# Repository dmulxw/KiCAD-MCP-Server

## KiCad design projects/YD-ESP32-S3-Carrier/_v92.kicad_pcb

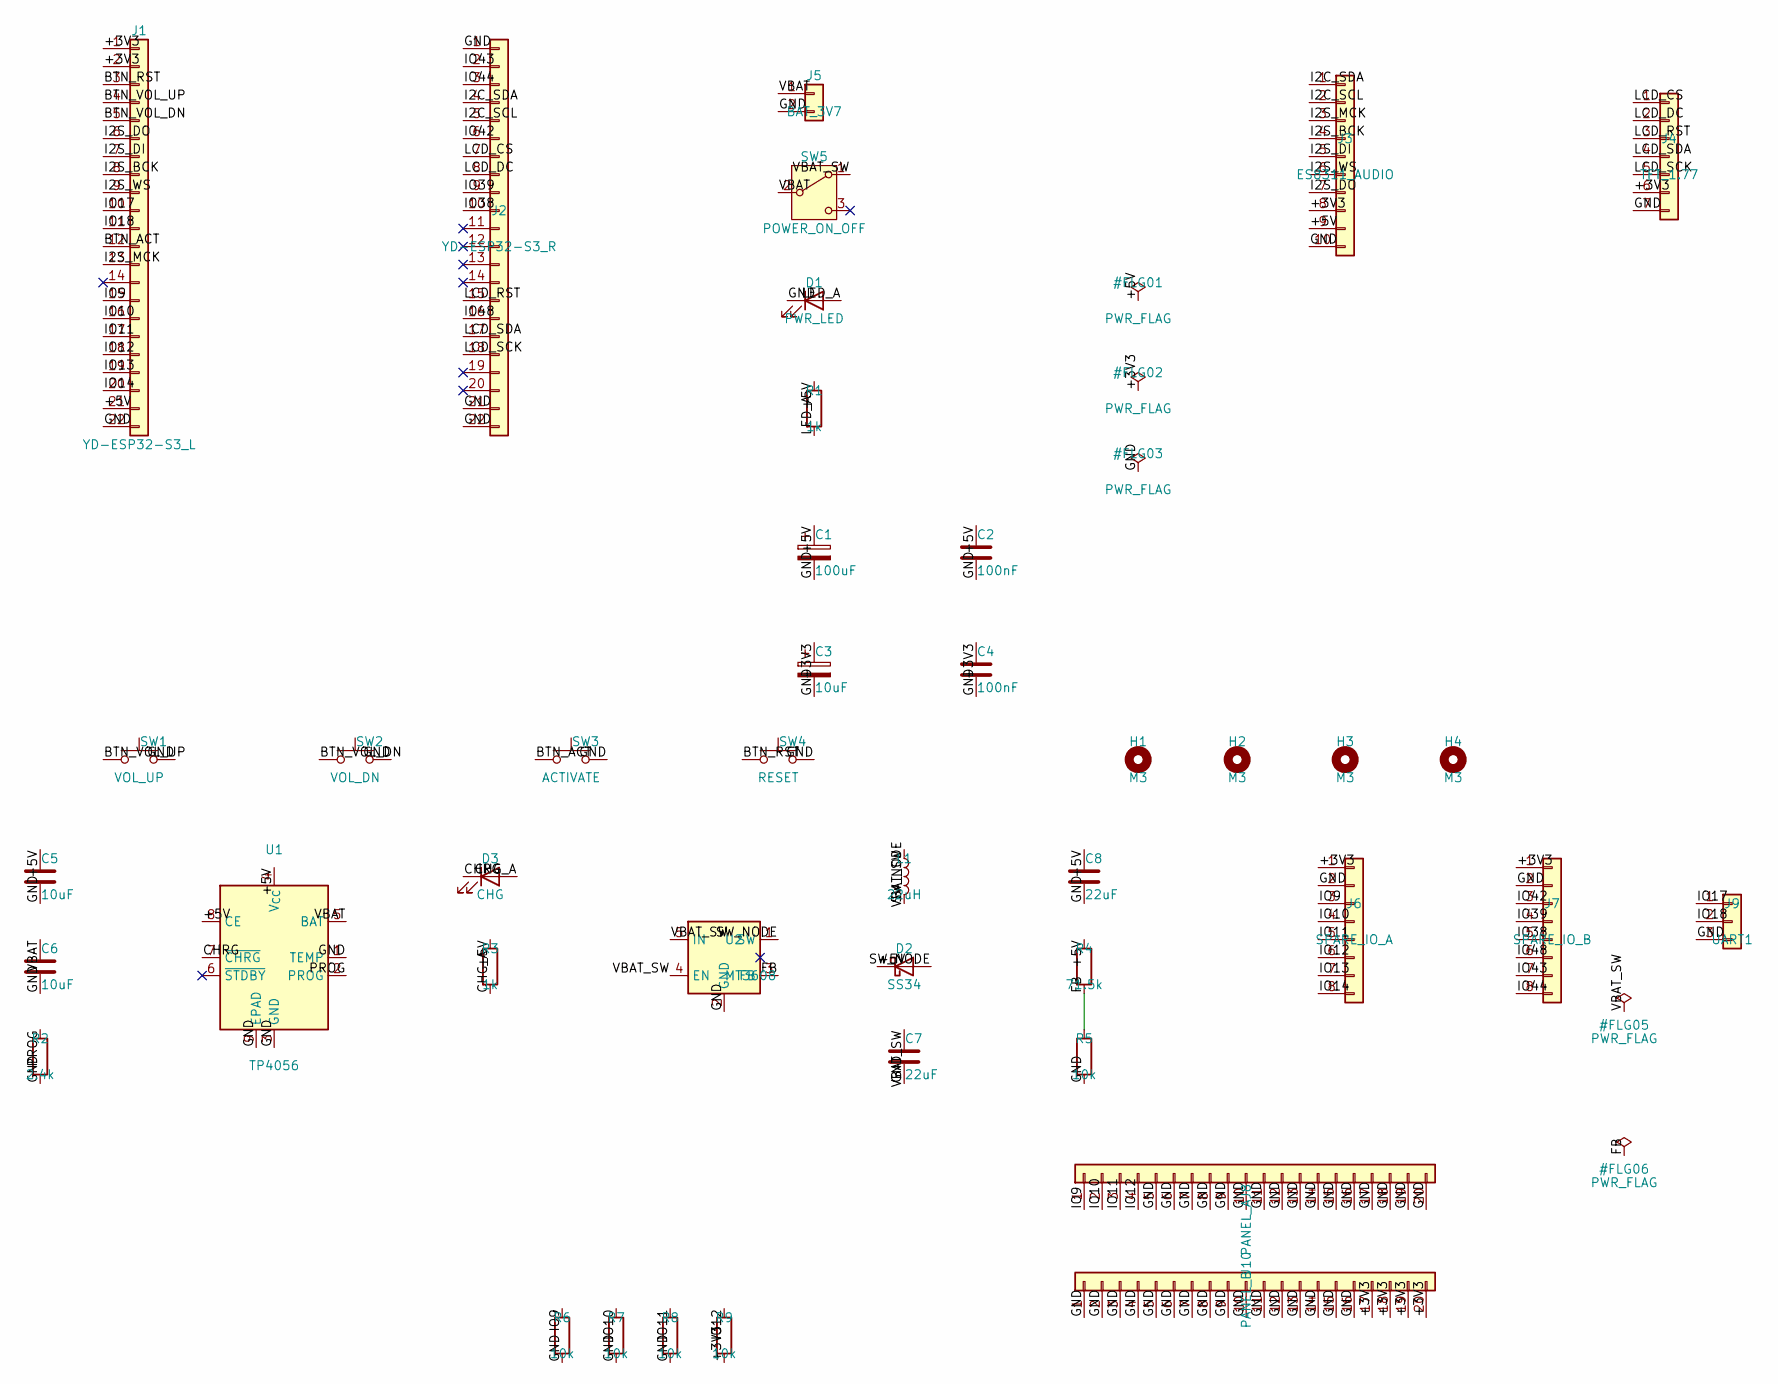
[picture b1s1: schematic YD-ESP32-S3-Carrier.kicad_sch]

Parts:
C1: 100uF; CP_Radial_D5.0mm_P2.50mm
C2, C4: 100nF; C_Disc_D5.0mm_W2.5mm_P5.00mm
C3: 10uF; CP_Radial_D5.0mm_P2.50mm
C5, C6: 10uF; C_1206_3216Metric
C7, C8: 22uF; C_1206_3216Metric
D1: PWR_LED; LED_D5.0mm
D2: SS34; D_SMA
D3: CHG; LED_0805_2012Metric
H1, H2, H3, H4: M3; MountingHole_3.2mm_M3
J1: YD-ESP32-S3_L; PinSocket_1x22_P2.54mm_Vertical
J2: YD-ESP32-S3_R; PinSocket_1x22_P2.54mm_Vertical
J3: ES8311_AUDIO; PinSocket_1x10_P2.54mm_Vertical
J4: TFT_1.77; PinHeader_1x07_P2.54mm_Vertical
J5: BAT_3V7; PinHeader_1x02_P2.54mm_Vertical
J6: SPARE_IO_A; PinHeader_1x08_P2.54mm_Vertical
J7: SPARE_IO_B; PinHeader_1x08_P2.54mm_Vertical
J8: PANEL_A; PinHeader_1x20_P2.54mm_Vertical
J9: UART1; PinHeader_1x03_P2.54mm_Vertical
J10: PANEL_B; PinHeader_1x20_P2.54mm_Vertical
L1: 22uH; L_Taiyo-Yuden_NR-60xx
R1: 1k; R_Axial_DIN0207_L6.3mm_D2.5mm_P7.62mm_Horizontal
R2: 2.4k; R_0805_2012Metric
R3: 1k; R_0805_2012Metric
R4: 71.5k; R_0805_2012Metric
R5: 10k; R_0805_2012Metric
R6, R7, R8, R9: 10k; R_0603_1608Metric
SW1: VOL_UP; SW_PUSH_6mm
SW2: VOL_DN; SW_PUSH_6mm
SW3: ACTIVATE; SW_PUSH_6mm
SW4: RESET; SW_PUSH_6mm
SW5: POWER_ON_OFF; SW_Slide_SPDT_Straight_CK_OS102011MS2Q
U1: TP4056; SOIC-8-1EP_3.9x4.9mm_P1.27mm_EP2.41x3.3mm_ThermalVias
U2: MT3608; SOT-23-6

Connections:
+3V3: C3.1, C4.1, J1.1, J1.2, J3.8, J4.6, J6.1, J7.1, J10.17, J10.18, J10.19, J10.20, R9.2
+5V: C1.1, C2.1, C5.1, C8.1, D2.1 (K), J1.21, J3.9, R1.1, R3.1, R4.1, U1.4 (V_{CC}), U1.8 (CE)
BTN_ACT: J1.12, SW3.1
BTN_RST: J1.3, SW4.1
BTN_VOL_DN: J1.5, SW2.1
BTN_VOL_UP: J1.4, SW1.1
CHG_A: D3.2 (A), R3.2
CHRG: D3.1 (K), U1.7 (~CHRG)
FB: R4.2, R5.1, U2.3 (FB)
GND: C1.2, C2.2, C3.2, C4.2, C5.2, C6.2, C7.2, C8.2, D1.1 (K), J1.22, J2.1, J2.21, J2.22, J3.10, J4.7, J5.2, J6.2, J7.2, J8.5, J8.6, J8.7, J8.8, J8.9, J8.10, J8.11, J8.12, J8.13, J8.14, J8.15, J8.16, J8.17, J8.18, J8.19, J8.20, J9.3, J10.1, J10.2, J10.3, J10.4, J10.5, J10.6, J10.7, J10.8, J10.9, J10.10, J10.11, J10.12, J10.13, J10.14, J10.15, J10.16, R2.2, R5.2, R6.2, R7.2, R8.2, SW1.2, SW2.2, SW3.2, SW4.2, U1.1 (TEMP), U1.3 (GND), U1.9 (EPAD), U2.2 (GND)
I2C_SCL: J2.5, J3.2
I2C_SDA: J2.4, J3.1
I2S_BCK: J1.8, J3.4
I2S_DI: J1.7, J3.5
I2S_DO: J1.6, J3.7
I2S_MCK: J1.13, J3.3
I2S_WS: J1.9, J3.6
IO9: J1.15, J6.3, J8.1, R6.1
IO10: J1.16, J6.4, J8.2, R7.1
IO11: J1.17, J6.5, J8.3, R8.1
IO12: J1.18, J6.6, J8.4, R9.1
IO13: J1.19, J6.7
IO14: J1.20, J6.8
IO17: J1.10, J9.1
IO18: J1.11, J9.2
IO38: J2.10, J7.5
IO39: J2.9, J7.4
IO42: J2.6, J7.3
IO43: J2.2, J7.7
IO44: J2.3, J7.8
IO48: J2.16, J7.6
LCD_CS: J2.7, J4.1
LCD_DC: J2.8, J4.2
LCD_RST: J2.15, J4.3
LCD_SCK: J2.18, J4.5
LCD_SDA: J2.17, J4.4
LED_A: D1.2 (A), R1.2
PROG: R2.1, U1.2 (PROG)
SW_NODE: D2.2 (A), L1.2, U2.1 (SW)
VBAT: C6.1, J5.1, SW5.2 (B), U1.5 (BAT)
VBAT_SW: C7.1, L1.1, SW5.1 (A), U2.4 (EN), U2.5 (IN)

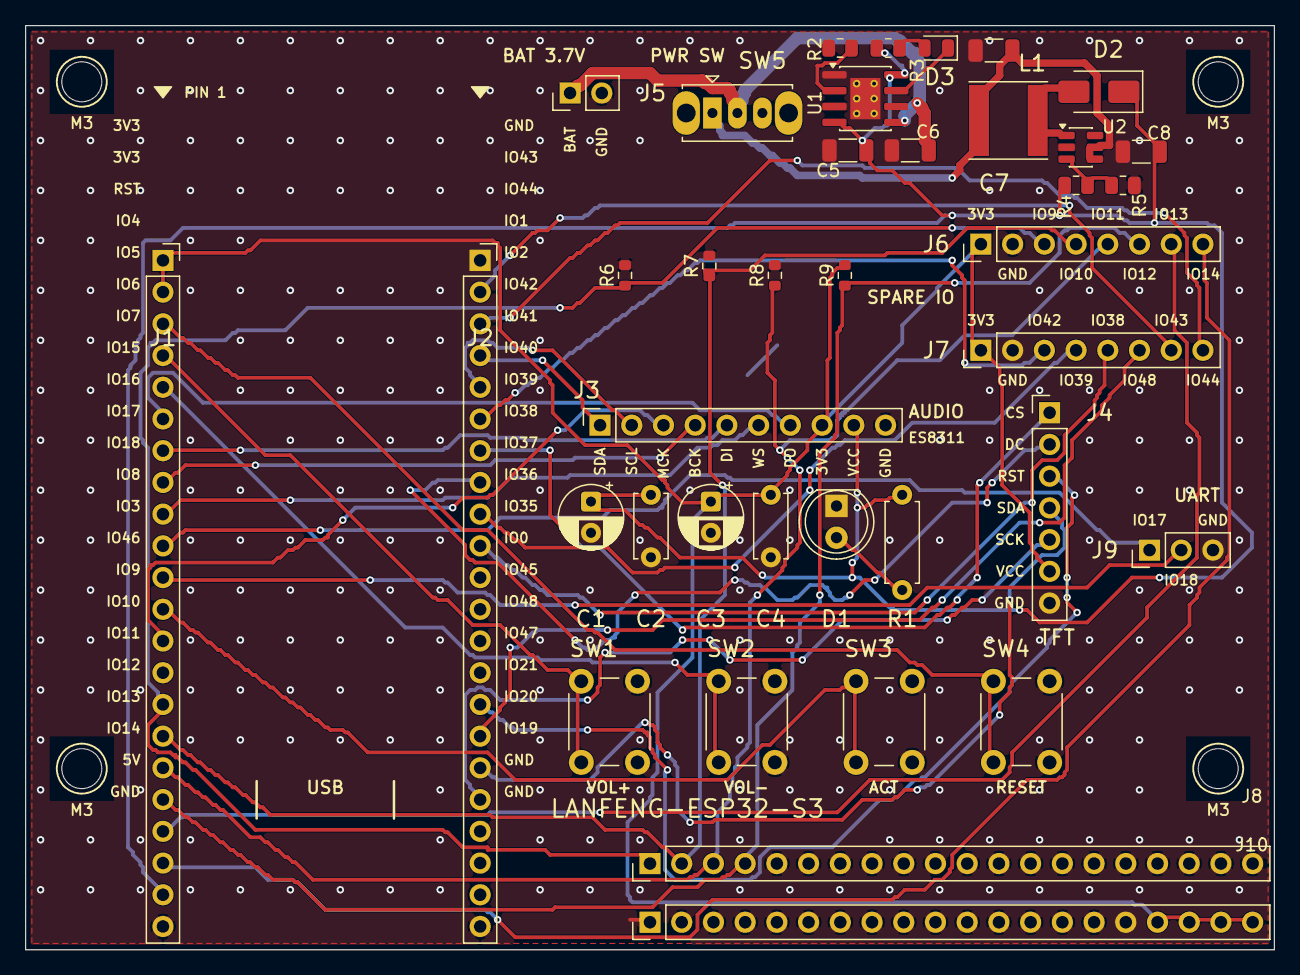
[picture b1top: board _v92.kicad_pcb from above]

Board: 2 copper layers, 100.0 x 74.0 mm, 42 parts (0 on the bottom side), 41 nets.

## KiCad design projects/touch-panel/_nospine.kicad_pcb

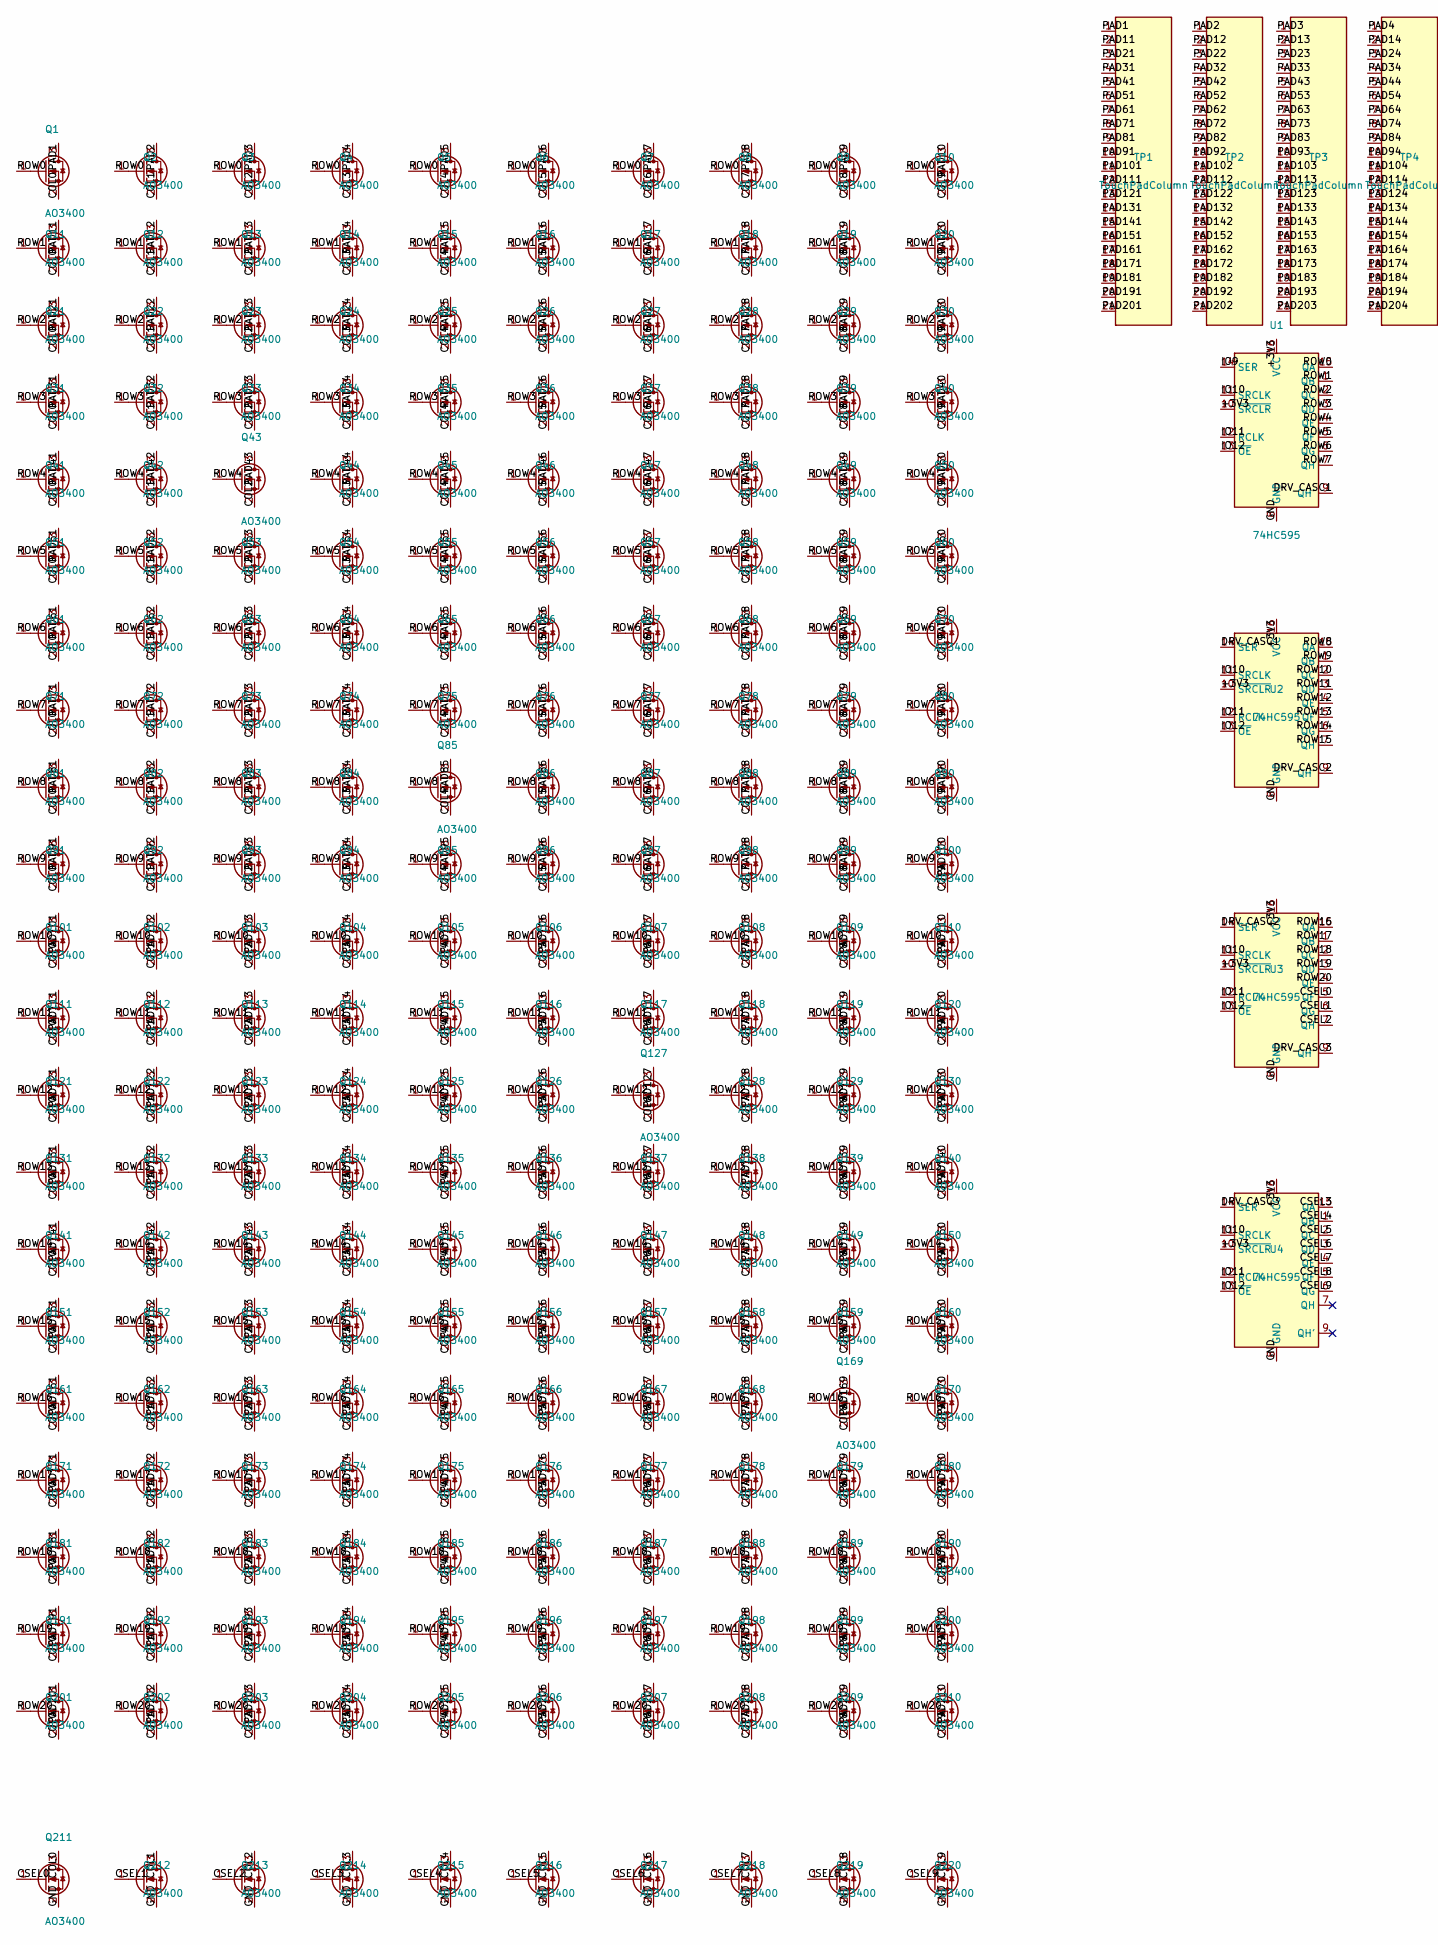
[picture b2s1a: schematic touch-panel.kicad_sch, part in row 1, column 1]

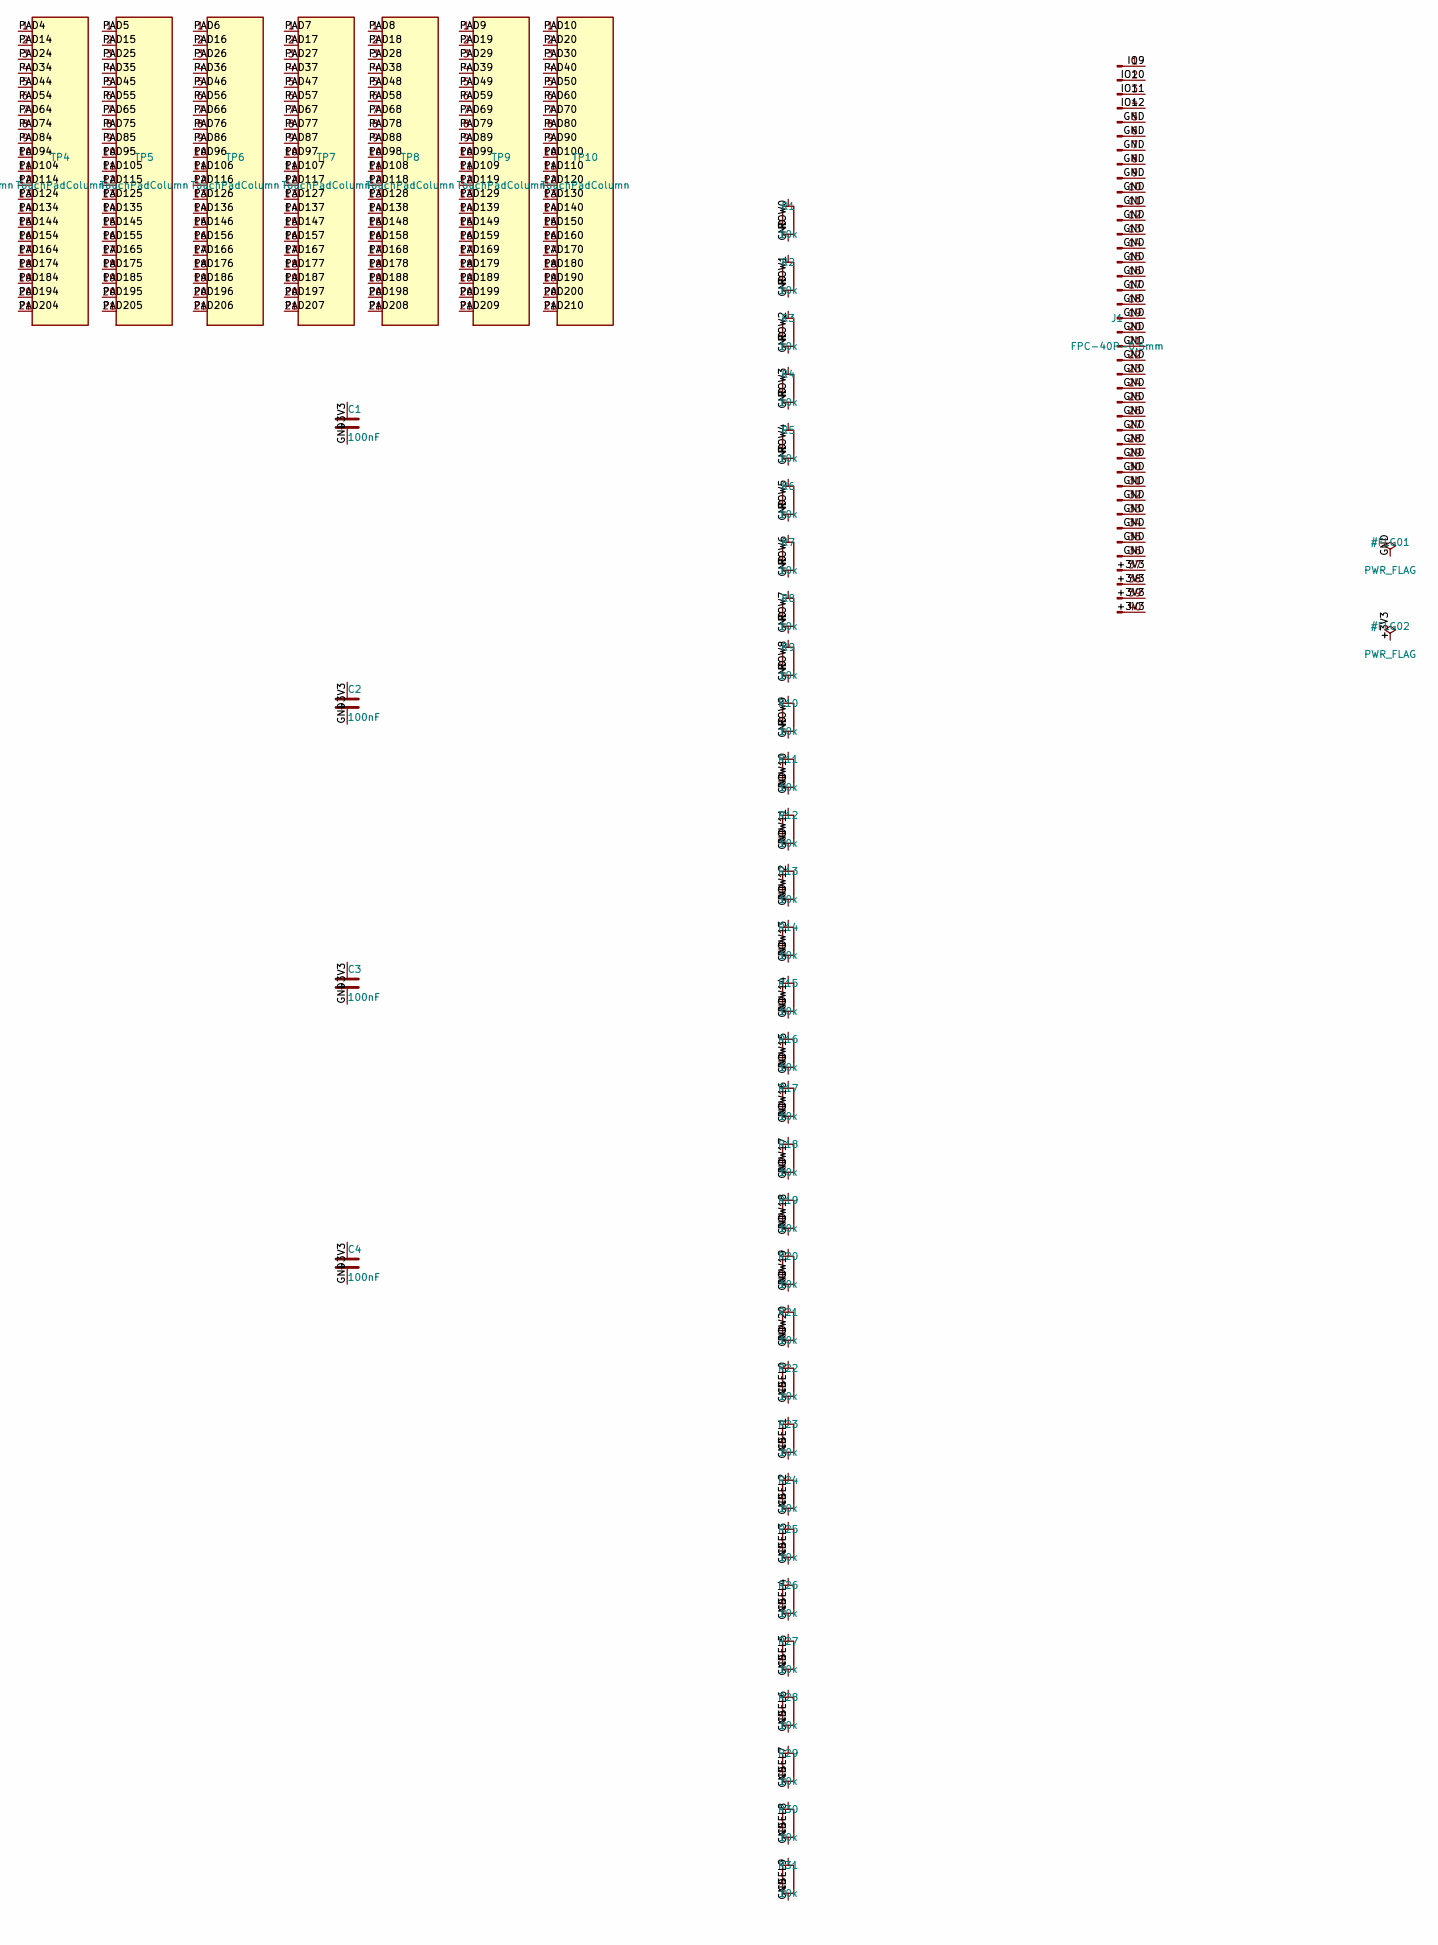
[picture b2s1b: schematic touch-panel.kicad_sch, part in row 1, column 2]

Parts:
C1, C2, C3, C4: 100nF; C_0402_1005Metric
J1: FPC-40P-0.5mm; Hirose_FH12-40S-0.5SH_1x40-1MP_P0.50mm_Horizontal
Q1, Q2, Q3, Q4, Q5, Q6, Q7, Q8, Q9, Q10, Q11, Q12, Q13, Q14, Q15, Q16, Q17, Q18, Q19, Q20, Q21, Q22, Q23, Q24, Q25, Q26, Q27, Q28, Q29, Q30, Q31, Q32, Q33, Q34, Q35, Q36, Q37, Q38, Q39, Q40, Q41, Q42, Q43, Q44, Q45, Q46, Q47, Q48, Q49, Q50, Q51, Q52, Q53, Q54, Q55, Q56, Q57, Q58, Q59, Q60, Q61, Q62, Q63, Q64, Q65, Q66, Q67, Q68, Q69, Q70, Q71, Q72, Q73, Q74, Q75, Q76, Q77, Q78, Q79, Q80, Q81, Q82, Q83, Q84, Q85, Q86, Q87, Q88, Q89, Q90, Q91, Q92, Q93, Q94, Q95, Q96, Q97, Q98, Q99, Q100, Q101, Q102, Q103, Q104, Q105, Q106, Q107, Q108, Q109, Q110, Q111, Q112, Q113, Q114, Q115, Q116, Q117, Q118, Q119, Q120, Q121, Q122, Q123, Q124, Q125, Q126, Q127, Q128, Q129, Q130, Q131, Q132, Q133, Q134, Q135, Q136, Q137, Q138, Q139, Q140, Q141, Q142, Q143, Q144, Q145, Q146, Q147, Q148, Q149, Q150, Q151, Q152, Q153, Q154, Q155, Q156, Q157, Q158, Q159, Q160, Q161, Q162, Q163, Q164, Q165, Q166, Q167, Q168, Q169, Q170, Q171, Q172, Q173, Q174, Q175, Q176, Q177, Q178, Q179, Q180, Q181, Q182, Q183, Q184, Q185, Q186, Q187, Q188, Q189, Q190, Q191, Q192, Q193, Q194, Q195, Q196, Q197, Q198, Q199, Q200, Q201, Q202, Q203, Q204, Q205, Q206, Q207, Q208, Q209, Q210, Q211, Q212, Q213, Q214, Q215, Q216, Q217, Q218, Q219, Q220: AO3400; SOT-23
R1, R2, R3, R4, R5, R6, R7, R8, R9, R10, R11, R12, R13, R14, R15, R16, R17, R18, R19, R20, R21, R22, R23, R24, R25, R26, R27, R28, R29, R30, R31: 10k; R_0402_1005Metric
TP1, TP2, TP3, TP4, TP5, TP6, TP7, TP8, TP9, TP10: TouchPadColumn
U1, U2, U3, U4: 74HC595; SOIC-16_3.9x9.9mm_P1.27mm

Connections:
+3V3: C1.1, C2.1, C3.1, C4.1, J1.37, J1.38, J1.39, J1.40, U1.10 (~SRCLR), U1.16 (VCC), U2.10 (~SRCLR), U2.16 (VCC), U3.10 (~SRCLR), U3.16 (VCC), U4.10 (~SRCLR), U4.16 (VCC)
COL0: Q1.2 (S), Q11.2 (S), Q21.2 (S), Q31.2 (S), Q41.2 (S), Q51.2 (S), Q61.2 (S), Q71.2 (S), Q81.2 (S), Q91.2 (S), Q101.2 (S), Q111.2 (S), Q121.2 (S), Q131.2 (S), Q141.2 (S), Q151.2 (S), Q161.2 (S), Q171.2 (S), Q181.2 (S), Q191.2 (S), Q201.2 (S), Q211.3 (D)
COL1: Q2.2 (S), Q12.2 (S), Q22.2 (S), Q32.2 (S), Q42.2 (S), Q52.2 (S), Q62.2 (S), Q72.2 (S), Q82.2 (S), Q92.2 (S), Q102.2 (S), Q112.2 (S), Q122.2 (S), Q132.2 (S), Q142.2 (S), Q152.2 (S), Q162.2 (S), Q172.2 (S), Q182.2 (S), Q192.2 (S), Q202.2 (S), Q212.3 (D)
COL2: Q3.2 (S), Q13.2 (S), Q23.2 (S), Q33.2 (S), Q43.2 (S), Q53.2 (S), Q63.2 (S), Q73.2 (S), Q83.2 (S), Q93.2 (S), Q103.2 (S), Q113.2 (S), Q123.2 (S), Q133.2 (S), Q143.2 (S), Q153.2 (S), Q163.2 (S), Q173.2 (S), Q183.2 (S), Q193.2 (S), Q203.2 (S), Q213.3 (D)
COL3: Q4.2 (S), Q14.2 (S), Q24.2 (S), Q34.2 (S), Q44.2 (S), Q54.2 (S), Q64.2 (S), Q74.2 (S), Q84.2 (S), Q94.2 (S), Q104.2 (S), Q114.2 (S), Q124.2 (S), Q134.2 (S), Q144.2 (S), Q154.2 (S), Q164.2 (S), Q174.2 (S), Q184.2 (S), Q194.2 (S), Q204.2 (S), Q214.3 (D)
COL4: Q5.2 (S), Q15.2 (S), Q25.2 (S), Q35.2 (S), Q45.2 (S), Q55.2 (S), Q65.2 (S), Q75.2 (S), Q85.2 (S), Q95.2 (S), Q105.2 (S), Q115.2 (S), Q125.2 (S), Q135.2 (S), Q145.2 (S), Q155.2 (S), Q165.2 (S), Q175.2 (S), Q185.2 (S), Q195.2 (S), Q205.2 (S), Q215.3 (D)
COL5: Q6.2 (S), Q16.2 (S), Q26.2 (S), Q36.2 (S), Q46.2 (S), Q56.2 (S), Q66.2 (S), Q76.2 (S), Q86.2 (S), Q96.2 (S), Q106.2 (S), Q116.2 (S), Q126.2 (S), Q136.2 (S), Q146.2 (S), Q156.2 (S), Q166.2 (S), Q176.2 (S), Q186.2 (S), Q196.2 (S), Q206.2 (S), Q216.3 (D)
COL6: Q7.2 (S), Q17.2 (S), Q27.2 (S), Q37.2 (S), Q47.2 (S), Q57.2 (S), Q67.2 (S), Q77.2 (S), Q87.2 (S), Q97.2 (S), Q107.2 (S), Q117.2 (S), Q127.2 (S), Q137.2 (S), Q147.2 (S), Q157.2 (S), Q167.2 (S), Q177.2 (S), Q187.2 (S), Q197.2 (S), Q207.2 (S), Q217.3 (D)
COL7: Q8.2 (S), Q18.2 (S), Q28.2 (S), Q38.2 (S), Q48.2 (S), Q58.2 (S), Q68.2 (S), Q78.2 (S), Q88.2 (S), Q98.2 (S), Q108.2 (S), Q118.2 (S), Q128.2 (S), Q138.2 (S), Q148.2 (S), Q158.2 (S), Q168.2 (S), Q178.2 (S), Q188.2 (S), Q198.2 (S), Q208.2 (S), Q218.3 (D)
COL8: Q9.2 (S), Q19.2 (S), Q29.2 (S), Q39.2 (S), Q49.2 (S), Q59.2 (S), Q69.2 (S), Q79.2 (S), Q89.2 (S), Q99.2 (S), Q109.2 (S), Q119.2 (S), Q129.2 (S), Q139.2 (S), Q149.2 (S), Q159.2 (S), Q169.2 (S), Q179.2 (S), Q189.2 (S), Q199.2 (S), Q209.2 (S), Q219.3 (D)
COL9: Q10.2 (S), Q20.2 (S), Q30.2 (S), Q40.2 (S), Q50.2 (S), Q60.2 (S), Q70.2 (S), Q80.2 (S), Q90.2 (S), Q100.2 (S), Q110.2 (S), Q120.2 (S), Q130.2 (S), Q140.2 (S), Q150.2 (S), Q160.2 (S), Q170.2 (S), Q180.2 (S), Q190.2 (S), Q200.2 (S), Q210.2 (S), Q220.3 (D)
CSEL0: Q211.1 (G), R22.1, U3.5 (QF)
CSEL1: Q212.1 (G), R23.1, U3.6 (QG)
CSEL2: Q213.1 (G), R24.1, U3.7 (QH)
CSEL3: Q214.1 (G), R25.1, U4.15 (QA); also elsewhere on the board
CSEL4: Q215.1 (G), R26.1, U4.1 (QB); also elsewhere on the board
CSEL5: Q216.1 (G), R27.1, U4.2 (QC); also elsewhere on the board
CSEL6: Q217.1 (G), R28.1, U4.3 (QD); also elsewhere on the board
CSEL7: Q218.1 (G), R29.1, U4.4 (QE)
CSEL8: Q219.1 (G), R30.1, U4.5 (QF)
CSEL9: Q220.1 (G), R31.1, U4.6 (QG)
DRV_CASC1: U1.9 (QH'), U2.14 (SER)
DRV_CASC2: U2.9 (QH'), U3.14 (SER)
DRV_CASC3: U3.9 (QH'), U4.14 (SER)
GND: C1.2, C2.2, C3.2, C4.2, J1.5, J1.6, J1.7, J1.8, J1.9, J1.10, J1.11, J1.12, J1.13, J1.14, J1.15, J1.16, J1.17, J1.18, J1.19, J1.20, J1.21, J1.22, J1.23, J1.24, J1.25, J1.26, J1.27, J1.28, J1.29, J1.30, J1.31, J1.32, J1.33, J1.34, J1.35, J1.36, Q211.2 (S), Q212.2 (S), Q213.2 (S), Q214.2 (S), Q215.2 (S), Q216.2 (S), Q217.2 (S), Q218.2 (S), Q219.2 (S), Q220.2 (S), R1.2, R2.2, R3.2, R4.2, R5.2, R6.2, R7.2, R8.2, R9.2, R10.2, R11.2, R12.2, R13.2, R14.2, R15.2, R16.2, R17.2, R18.2, R19.2, R20.2, R21.2, R22.2, R23.2, R24.2, R25.2, R26.2, R27.2, R28.2, R29.2, R30.2, R31.2, U1.8 (GND), U2.8 (GND), U3.8 (GND), U4.8 (GND); also elsewhere on the board
IO9: J1.1, U1.14 (SER)
IO10: J1.2, U1.11 (SRCLK), U2.11 (SRCLK), U3.11 (SRCLK), U4.11 (SRCLK)
IO11: J1.3, U1.12 (RCLK), U2.12 (RCLK), U3.12 (RCLK), U4.12 (RCLK)
IO12: J1.4, U1.13 (~OE), U2.13 (~OE), U3.13 (~OE), U4.13 (~OE)
PAD1: Q1.3 (D), TP1.1
PAD2: Q2.3 (D), TP2.1
PAD3: Q3.3 (D), TP3.1
PAD4: Q4.3 (D), TP4.1
PAD5: Q5.3 (D), TP5.1
PAD6: Q6.3 (D), TP6.1
PAD7: Q7.3 (D), TP7.1
PAD8: Q8.3 (D), TP8.1
PAD9: Q9.3 (D), TP9.1
PAD10: Q10.3 (D), TP10.1
PAD11: Q11.3 (D), TP1.2
PAD12: Q12.3 (D), TP2.2
PAD13: Q13.3 (D), TP3.2
PAD14: Q14.3 (D), TP4.2
PAD15: Q15.3 (D), TP5.2
PAD16: Q16.3 (D), TP6.2
PAD17: Q17.3 (D), TP7.2
PAD18: Q18.3 (D), TP8.2
PAD19: Q19.3 (D), TP9.2
PAD20: Q20.3 (D), TP10.2
PAD21: Q21.3 (D), TP1.3
PAD22: Q22.3 (D), TP2.3
PAD23: Q23.3 (D), TP3.3
PAD24: Q24.3 (D), TP4.3
PAD25: Q25.3 (D), TP5.3
PAD26: Q26.3 (D), TP6.3
PAD27: Q27.3 (D), TP7.3
PAD28: Q28.3 (D), TP8.3
PAD29: Q29.3 (D), TP9.3
PAD30: Q30.3 (D), TP10.3
PAD31: Q31.3 (D), TP1.4
PAD32: Q32.3 (D), TP2.4
PAD33: Q33.3 (D), TP3.4
PAD34: Q34.3 (D), TP4.4
PAD35: Q35.3 (D), TP5.4
PAD36: Q36.3 (D), TP6.4
PAD37: Q37.3 (D), TP7.4
PAD38: Q38.3 (D), TP8.4
PAD39: Q39.3 (D), TP9.4
PAD40: Q40.3 (D), TP10.4
PAD41: Q41.3 (D), TP1.5
PAD42: Q42.3 (D), TP2.5
PAD43: Q43.3 (D), TP3.5
PAD44: Q44.3 (D), TP4.5
PAD45: Q45.3 (D), TP5.5
PAD46: Q46.3 (D), TP6.5
PAD47: Q47.3 (D), TP7.5
PAD48: Q48.3 (D), TP8.5
PAD49: Q49.3 (D), TP9.5
PAD50: Q50.3 (D), TP10.5
PAD51: Q51.3 (D), TP1.6
PAD52: Q52.3 (D), TP2.6
PAD53: Q53.3 (D), TP3.6
PAD54: Q54.3 (D), TP4.6
PAD55: Q55.3 (D), TP5.6
PAD56: Q56.3 (D), TP6.6
PAD57: Q57.3 (D), TP7.6
PAD58: Q58.3 (D), TP8.6
PAD59: Q59.3 (D), TP9.6
PAD60: Q60.3 (D), TP10.6
PAD61: Q61.3 (D), TP1.7
PAD62: Q62.3 (D), TP2.7
PAD63: Q63.3 (D), TP3.7
PAD64: Q64.3 (D), TP4.7
PAD65: Q65.3 (D), TP5.7
PAD66: Q66.3 (D), TP6.7
PAD67: Q67.3 (D), TP7.7
PAD68: Q68.3 (D), TP8.7
PAD69: Q69.3 (D), TP9.7
PAD70: Q70.3 (D), TP10.7
PAD71: Q71.3 (D), TP1.8
PAD72: Q72.3 (D), TP2.8
PAD73: Q73.3 (D), TP3.8
PAD74: Q74.3 (D), TP4.8
PAD75: Q75.3 (D), TP5.8
PAD76: Q76.3 (D), TP6.8
PAD77: Q77.3 (D), TP7.8
PAD78: Q78.3 (D), TP8.8
PAD79: Q79.3 (D), TP9.8
PAD80: Q80.3 (D), TP10.8
PAD81: Q81.3 (D), TP1.9
PAD82: Q82.3 (D), TP2.9
PAD83: Q83.3 (D), TP3.9
PAD84: Q84.3 (D), TP4.9
PAD85: Q85.3 (D), TP5.9
PAD86: Q86.3 (D), TP6.9
PAD87: Q87.3 (D), TP7.9
PAD88: Q88.3 (D), TP8.9
PAD89: Q89.3 (D), TP9.9
PAD90: Q90.3 (D), TP10.9
PAD91: Q91.3 (D), TP1.10
PAD92: Q92.3 (D), TP2.10
PAD93: Q93.3 (D), TP3.10
PAD94: Q94.3 (D), TP4.10
PAD95: Q95.3 (D), TP5.10
PAD96: Q96.3 (D), TP6.10
PAD97: Q97.3 (D), TP7.10
PAD98: Q98.3 (D), TP8.10
PAD99: Q99.3 (D), TP9.10
PAD100: Q100.3 (D), TP10.10
PAD101: Q101.3 (D), TP1.11
PAD102: Q102.3 (D), TP2.11
PAD103: Q103.3 (D), TP3.11
PAD104: Q104.3 (D), TP4.11
PAD105: Q105.3 (D), TP5.11
PAD106: Q106.3 (D), TP6.11
PAD107: Q107.3 (D), TP7.11
PAD108: Q108.3 (D), TP8.11
PAD109: Q109.3 (D), TP9.11
PAD110: Q110.3 (D), TP10.11
PAD111: Q111.3 (D), TP1.12
PAD112: Q112.3 (D), TP2.12
PAD113: Q113.3 (D), TP3.12
PAD114: Q114.3 (D), TP4.12
PAD115: Q115.3 (D), TP5.12
PAD116: Q116.3 (D), TP6.12
PAD117: Q117.3 (D), TP7.12
PAD118: Q118.3 (D), TP8.12
PAD119: Q119.3 (D), TP9.12
PAD120: Q120.3 (D), TP10.12
PAD121: Q121.3 (D), TP1.13
PAD122: Q122.3 (D), TP2.13
PAD123: Q123.3 (D), TP3.13
PAD124: Q124.3 (D), TP4.13
PAD125: Q125.3 (D), TP5.13
PAD126: Q126.3 (D), TP6.13
PAD127: Q127.3 (D), TP7.13
PAD128: Q128.3 (D), TP8.13
PAD129: Q129.3 (D), TP9.13
PAD130: Q130.3 (D), TP10.13
PAD131: Q131.3 (D), TP1.14
PAD132: Q132.3 (D), TP2.14
PAD133: Q133.3 (D), TP3.14
PAD134: Q134.3 (D), TP4.14
PAD135: Q135.3 (D), TP5.14
PAD136: Q136.3 (D), TP6.14
PAD137: Q137.3 (D), TP7.14
PAD138: Q138.3 (D), TP8.14
PAD139: Q139.3 (D), TP9.14
PAD140: Q140.3 (D), TP10.14
PAD141: Q141.3 (D), TP1.15
PAD142: Q142.3 (D), TP2.15
PAD143: Q143.3 (D), TP3.15
PAD144: Q144.3 (D), TP4.15
PAD145: Q145.3 (D), TP5.15
PAD146: Q146.3 (D), TP6.15
PAD147: Q147.3 (D), TP7.15
PAD148: Q148.3 (D), TP8.15
PAD149: Q149.3 (D), TP9.15
PAD150: Q150.3 (D), TP10.15
PAD151: Q151.3 (D), TP1.16
PAD152: Q152.3 (D), TP2.16
PAD153: Q153.3 (D), TP3.16
PAD154: Q154.3 (D), TP4.16
PAD155: Q155.3 (D), TP5.16
PAD156: Q156.3 (D), TP6.16
PAD157: Q157.3 (D), TP7.16
PAD158: Q158.3 (D), TP8.16
PAD159: Q159.3 (D), TP9.16
PAD160: Q160.3 (D), TP10.16
PAD161: Q161.3 (D), TP1.17
PAD162: Q162.3 (D), TP2.17
PAD163: Q163.3 (D), TP3.17
PAD164: Q164.3 (D), TP4.17
PAD165: Q165.3 (D), TP5.17
PAD166: Q166.3 (D), TP6.17
PAD167: Q167.3 (D), TP7.17
PAD168: Q168.3 (D), TP8.17
PAD169: Q169.3 (D), TP9.17
PAD170: Q170.3 (D), TP10.17
PAD171: Q171.3 (D), TP1.18
PAD172: Q172.3 (D), TP2.18
PAD173: Q173.3 (D), TP3.18
PAD174: Q174.3 (D), TP4.18
PAD175: Q175.3 (D), TP5.18
PAD176: Q176.3 (D), TP6.18
PAD177: Q177.3 (D), TP7.18
PAD178: Q178.3 (D), TP8.18
PAD179: Q179.3 (D), TP9.18
PAD180: Q180.3 (D), TP10.18
PAD181: Q181.3 (D), TP1.19
PAD182: Q182.3 (D), TP2.19
PAD183: Q183.3 (D), TP3.19
PAD184: Q184.3 (D), TP4.19
PAD185: Q185.3 (D), TP5.19
PAD186: Q186.3 (D), TP6.19
PAD187: Q187.3 (D), TP7.19
PAD188: Q188.3 (D), TP8.19
PAD189: Q189.3 (D), TP9.19
PAD190: Q190.3 (D), TP10.19
PAD191: Q191.3 (D), TP1.20
PAD192: Q192.3 (D), TP2.20
PAD193: Q193.3 (D), TP3.20
PAD194: Q194.3 (D), TP4.20
PAD195: Q195.3 (D), TP5.20
PAD196: Q196.3 (D), TP6.20
PAD197: Q197.3 (D), TP7.20
PAD198: Q198.3 (D), TP8.20
PAD199: Q199.3 (D), TP9.20
PAD200: Q200.3 (D), TP10.20
PAD201: Q201.3 (D), TP1.21
PAD202: Q202.3 (D), TP2.21
PAD203: Q203.3 (D), TP3.21
PAD204: Q204.3 (D), TP4.21
PAD205: Q205.3 (D), TP5.21
PAD206: Q206.3 (D), TP6.21
PAD207: Q207.3 (D), TP7.21
PAD208: Q208.3 (D), TP8.21
PAD209: Q209.3 (D), TP9.21
PAD210: Q210.3 (D), TP10.21
ROW0: Q1.1 (G), Q2.1 (G), Q3.1 (G), Q4.1 (G), Q5.1 (G), Q6.1 (G), Q7.1 (G), Q8.1 (G), Q9.1 (G), Q10.1 (G), R1.1, U1.15 (QA); also elsewhere on the board
ROW1: Q11.1 (G), Q12.1 (G), Q13.1 (G), Q14.1 (G), Q15.1 (G), Q16.1 (G), Q17.1 (G), Q18.1 (G), Q19.1 (G), Q20.1 (G), R2.1, U1.1 (QB); also elsewhere on the board
ROW2: Q21.1 (G), Q22.1 (G), Q23.1 (G), Q24.1 (G), Q25.1 (G), Q26.1 (G), Q27.1 (G), Q28.1 (G), Q29.1 (G), Q30.1 (G), R3.1, U1.2 (QC)
ROW3: Q31.1 (G), Q32.1 (G), Q33.1 (G), Q34.1 (G), Q35.1 (G), Q36.1 (G), Q37.1 (G), Q38.1 (G), Q39.1 (G), Q40.1 (G), R4.1, U1.3 (QD); also elsewhere on the board
ROW4: Q41.1 (G), Q42.1 (G), Q43.1 (G), Q44.1 (G), Q45.1 (G), Q46.1 (G), Q47.1 (G), Q48.1 (G), Q49.1 (G), Q50.1 (G), R5.1, U1.4 (QE)
ROW5: Q51.1 (G), Q52.1 (G), Q53.1 (G), Q54.1 (G), Q55.1 (G), Q56.1 (G), Q57.1 (G), Q58.1 (G), Q59.1 (G), Q60.1 (G), R6.1, U1.5 (QF); also elsewhere on the board
ROW6: Q61.1 (G), Q62.1 (G), Q63.1 (G), Q64.1 (G), Q65.1 (G), Q66.1 (G), Q67.1 (G), Q68.1 (G), Q69.1 (G), Q70.1 (G), R7.1, U1.6 (QG); also elsewhere on the board
ROW7: Q71.1 (G), Q72.1 (G), Q73.1 (G), Q74.1 (G), Q75.1 (G), Q76.1 (G), Q77.1 (G), Q78.1 (G), Q79.1 (G), Q80.1 (G), R8.1, U1.7 (QH); also elsewhere on the board
ROW8: Q81.1 (G), Q82.1 (G), Q83.1 (G), Q84.1 (G), Q85.1 (G), Q86.1 (G), Q87.1 (G), Q88.1 (G), Q89.1 (G), Q90.1 (G), R9.1, U2.15 (QA)
ROW9: Q91.1 (G), Q92.1 (G), Q93.1 (G), Q94.1 (G), Q95.1 (G), Q96.1 (G), Q97.1 (G), Q98.1 (G), Q99.1 (G), Q100.1 (G), R10.1, U2.1 (QB); also elsewhere on the board
ROW10: Q101.1 (G), Q102.1 (G), Q103.1 (G), Q104.1 (G), Q105.1 (G), Q106.1 (G), Q107.1 (G), Q108.1 (G), Q109.1 (G), Q110.1 (G), R11.1, U2.2 (QC); also elsewhere on the board
ROW11: Q111.1 (G), Q112.1 (G), Q113.1 (G), Q114.1 (G), Q115.1 (G), Q116.1 (G), Q117.1 (G), Q118.1 (G), Q119.1 (G), Q120.1 (G), R12.1, U2.3 (QD)
ROW12: Q121.1 (G), Q122.1 (G), Q123.1 (G), Q124.1 (G), Q125.1 (G), Q126.1 (G), Q127.1 (G), Q128.1 (G), Q129.1 (G), Q130.1 (G), R13.1, U2.4 (QE)
ROW13: Q131.1 (G), Q132.1 (G), Q133.1 (G), Q134.1 (G), Q135.1 (G), Q136.1 (G), Q137.1 (G), Q138.1 (G), Q139.1 (G), Q140.1 (G), R14.1, U2.5 (QF)
ROW14: Q141.1 (G), Q142.1 (G), Q143.1 (G), Q144.1 (G), Q145.1 (G), Q146.1 (G), Q147.1 (G), Q148.1 (G), Q149.1 (G), Q150.1 (G), R15.1, U2.6 (QG)
ROW15: Q151.1 (G), Q152.1 (G), Q153.1 (G), Q154.1 (G), Q155.1 (G), Q156.1 (G), Q157.1 (G), Q158.1 (G), Q159.1 (G), Q160.1 (G), R16.1, U2.7 (QH)
ROW16: Q161.1 (G), Q162.1 (G), Q163.1 (G), Q164.1 (G), Q165.1 (G), Q166.1 (G), Q167.1 (G), Q168.1 (G), Q169.1 (G), Q170.1 (G), R17.1, U3.15 (QA)
ROW17: Q171.1 (G), Q172.1 (G), Q173.1 (G), Q174.1 (G), Q175.1 (G), Q176.1 (G), Q177.1 (G), Q178.1 (G), Q179.1 (G), Q180.1 (G), R18.1, U3.1 (QB)
ROW18: Q181.1 (G), Q182.1 (G), Q183.1 (G), Q184.1 (G), Q185.1 (G), Q186.1 (G), Q187.1 (G), Q188.1 (G), Q189.1 (G), Q190.1 (G), R19.1, U3.2 (QC)
ROW19: Q191.1 (G), Q192.1 (G), Q193.1 (G), Q194.1 (G), Q195.1 (G), Q196.1 (G), Q197.1 (G), Q198.1 (G), Q199.1 (G), Q200.1 (G), R20.1, U3.3 (QD)
ROW20: Q201.1 (G), Q202.1 (G), Q203.1 (G), Q204.1 (G), Q205.1 (G), Q206.1 (G), Q207.1 (G), Q208.1 (G), Q209.1 (G), Q210.1 (G), R21.1, U3.4 (QE)

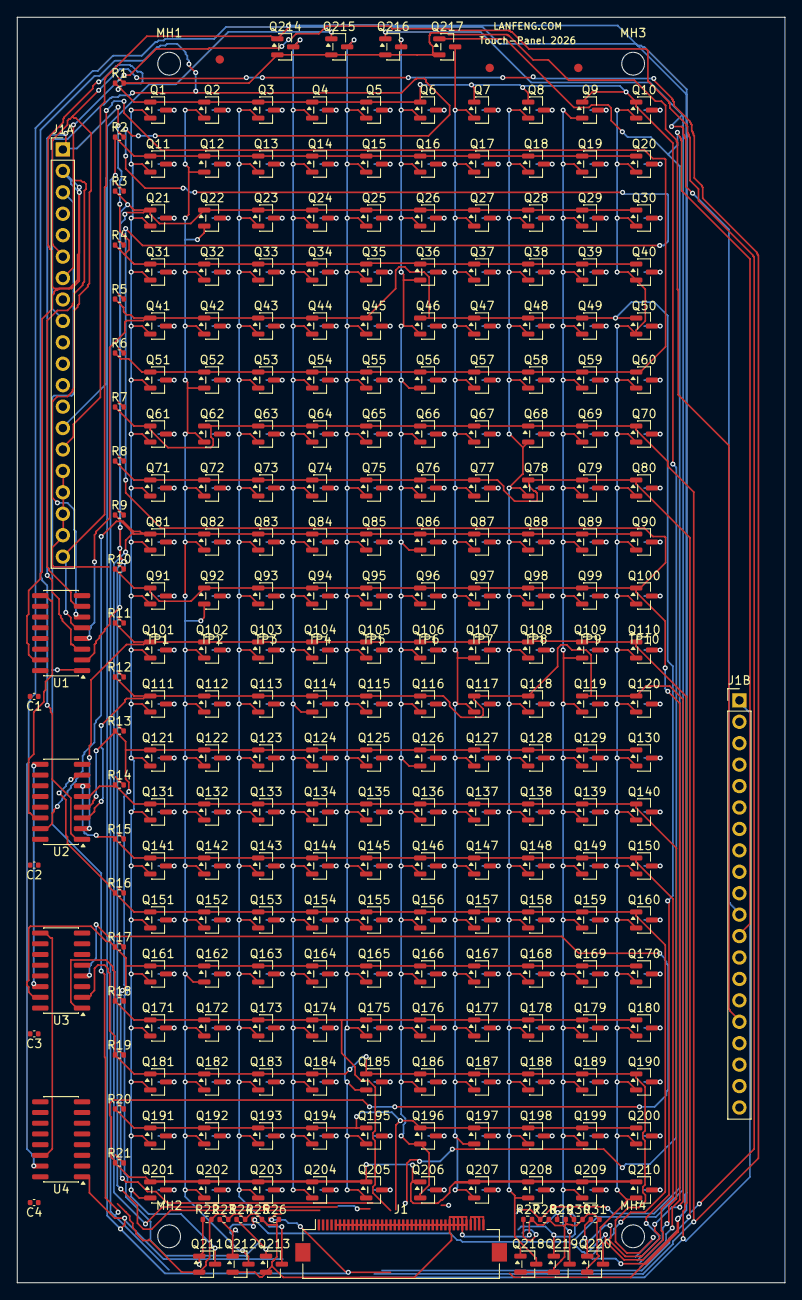
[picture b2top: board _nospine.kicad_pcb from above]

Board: 2 copper layers, 91.0 x 150.0 mm, 279 parts (0 on the bottom side), 260 nets.

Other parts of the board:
J1A, J1B: PinHeader_1x20_P2.54mm_Vertical
MH1, MH2, MH3, MH4: MountingHole_2.7mm
MK1, MK2, MK3: Fiducial_1mm_Mask2mm

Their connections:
CSEL3: J1A.15; also elsewhere on the board
CSEL4: J1A.14; also elsewhere on the board
CSEL5: J1B.11; also elsewhere on the board
CSEL6: J1B.12; also elsewhere on the board
GND: J1A.16, J1A.17, J1A.18, J1A.19, J1B.16; also elsewhere on the board
ROW0: J1A.2; also elsewhere on the board
ROW1: J1A.3; also elsewhere on the board
ROW3: J1A.1; also elsewhere on the board
ROW5: J1A.20; also elsewhere on the board
ROW6: J1A.6; also elsewhere on the board
ROW7: J1A.7; also elsewhere on the board
ROW9: J1A.9; also elsewhere on the board
ROW10: J1B.1; also elsewhere on the board
